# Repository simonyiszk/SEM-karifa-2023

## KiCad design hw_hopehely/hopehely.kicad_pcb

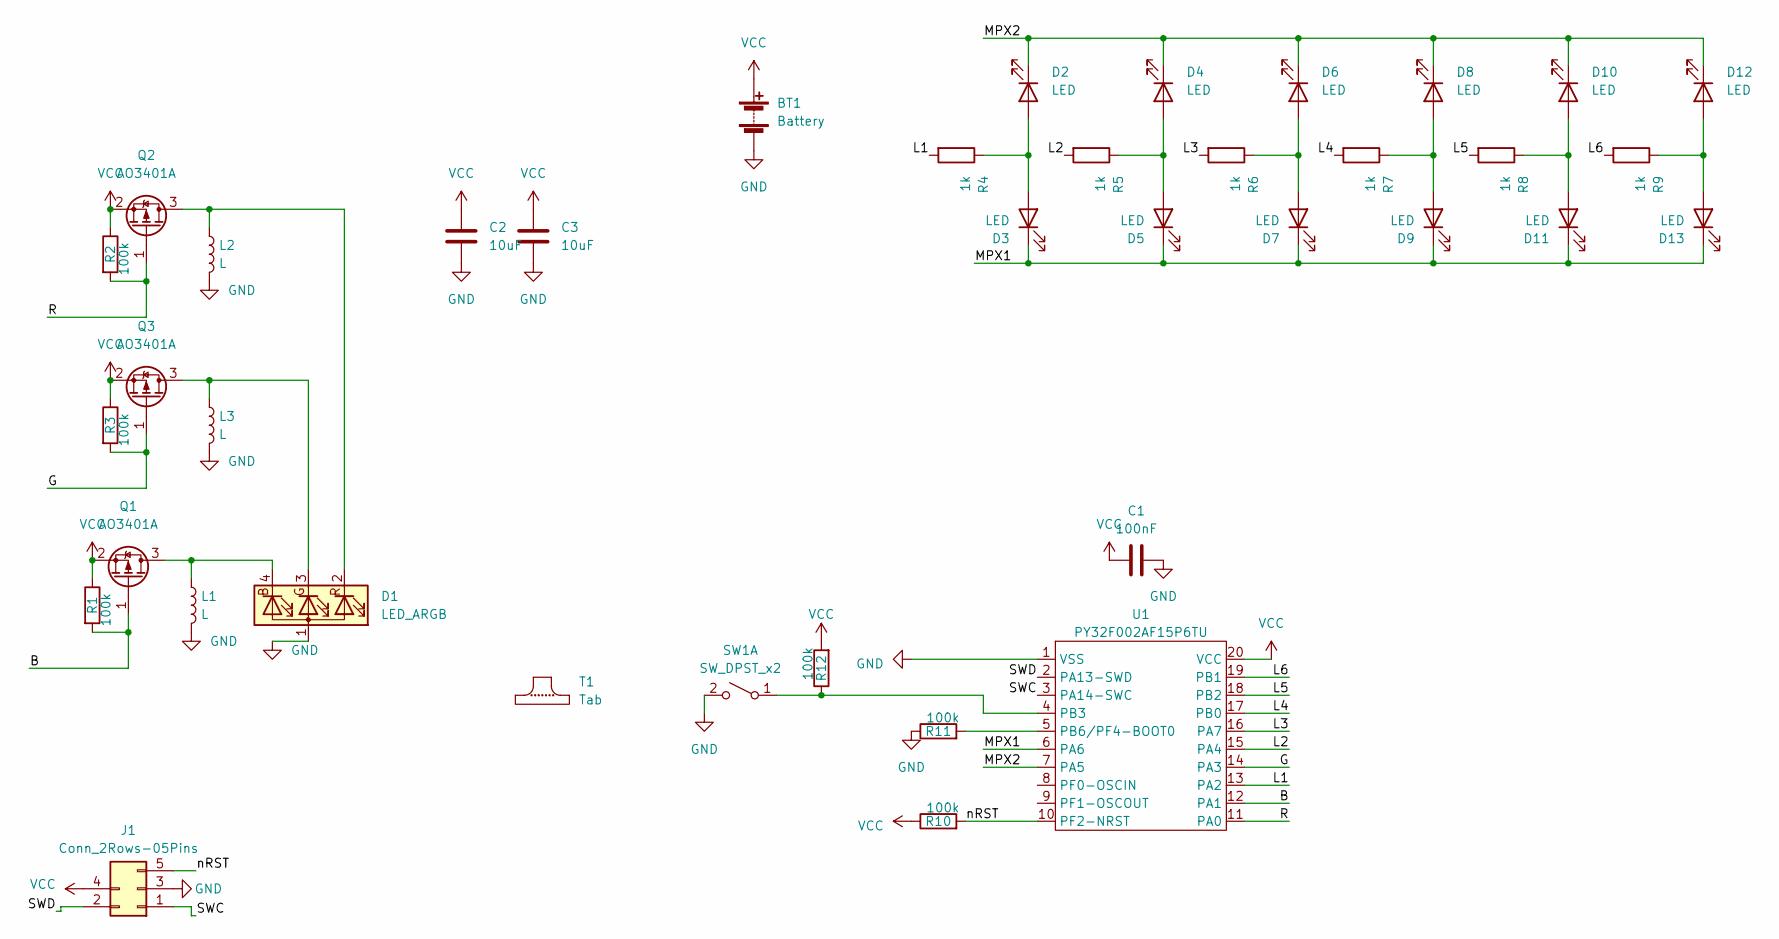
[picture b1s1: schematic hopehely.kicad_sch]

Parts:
BT1: Battery; CR2032_Holder
C1: 100nF; C_0805_2012Metric
C2, C3: 10uF; C_0805_2012Metric
D1: LED_ARGB; LED_RGB_Wuerth-PLCC4_3.2x2.8mm_150141M173100
D2, D3, D4, D5, D6, D7, D8, D9, D10, D11, D12, D13: LED; LED_0805_2012Metric
J1: Conn_2Rows-05Pins; ProgConnector_5pin
L1, L2, L3: L; L_1008_2520Metric
Q1, Q2, Q3: AO3401A; SOT-23
R1, R2, R3, R10, R11, R12: 100k; R_0603_1608Metric
R4, R5, R6, R7, R8, R9: 1k; R_0603_1608Metric
SW1: SW_DPST_x2; SW_SPST_TL3342
T1: Tab
U1: PY32F002AF15P6TU; TSSOP-20_4.4x6.5mm_P0.65mm

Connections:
/B: Q1.1 (G), R1.2, U1.12 (PA1)
/G: Q3.1 (G), R3.2, U1.14 (PA3)
/L1: R4.2, U1.13 (PA2)
/L2: R5.2, U1.15 (PA4)
/L3: R6.2, U1.16 (PA7)
/L4: R7.2, U1.17 (PB0)
/L5: R8.2, U1.18 (PB2)
/L6: R9.2, U1.19 (PB1)
/MPX1: D3.1 (K), D5.1 (K), D7.1 (K), D9.1 (K), D11.1 (K), D13.1 (K), U1.6 (PA6)
/MPX2: D2.1 (K), D4.1 (K), D6.1 (K), D8.1 (K), D10.1 (K), D12.1 (K), U1.7 (PA5)
/R: Q2.1 (G), R2.2, U1.11 (PA0)
/SWC: J1.1, U1.3 (PA14-SWC)
/SWD: J1.2, U1.2 (PA13-SWD)
/nRST: J1.5, R10.2, U1.10 (PF2-NRST)
GND: BT1.2 (-), C1.1, C2.2, C3.2, D1.1 (A), J1.3, L1.2, L2.2, L3.2, R11.1, SW1.2 (B), U1.1 (VSS)
unnamed: D1.4 (BK), L1.1, Q1.3 (D)
unnamed: D1.3 (GK), L3.1, Q3.3 (D)
unnamed: D1.2 (RK), L2.1, Q2.3 (D)
unnamed: D2.2 (A), D3.2 (A), R4.1
unnamed: D4.2 (A), D5.2 (A), R5.1
unnamed: D6.2 (A), D7.2 (A), R6.1
unnamed: D8.2 (A), D9.2 (A), R7.1
unnamed: D10.2 (A), D11.2 (A), R8.1
unnamed: D12.2 (A), D13.2 (A), R9.1
unnamed: R12.1, SW1.1 (A), U1.4 (PB3)
unnamed: R11.2, U1.5 (PB6/PF4-BOOT0)
VCC: BT1.1 (+), C1.2, C2.1, C3.1, J1.4, Q1.2 (S), Q2.2 (S), Q3.2 (S), R1.1, R2.1, R3.1, R10.1, R12.2, U1.20 (VCC)

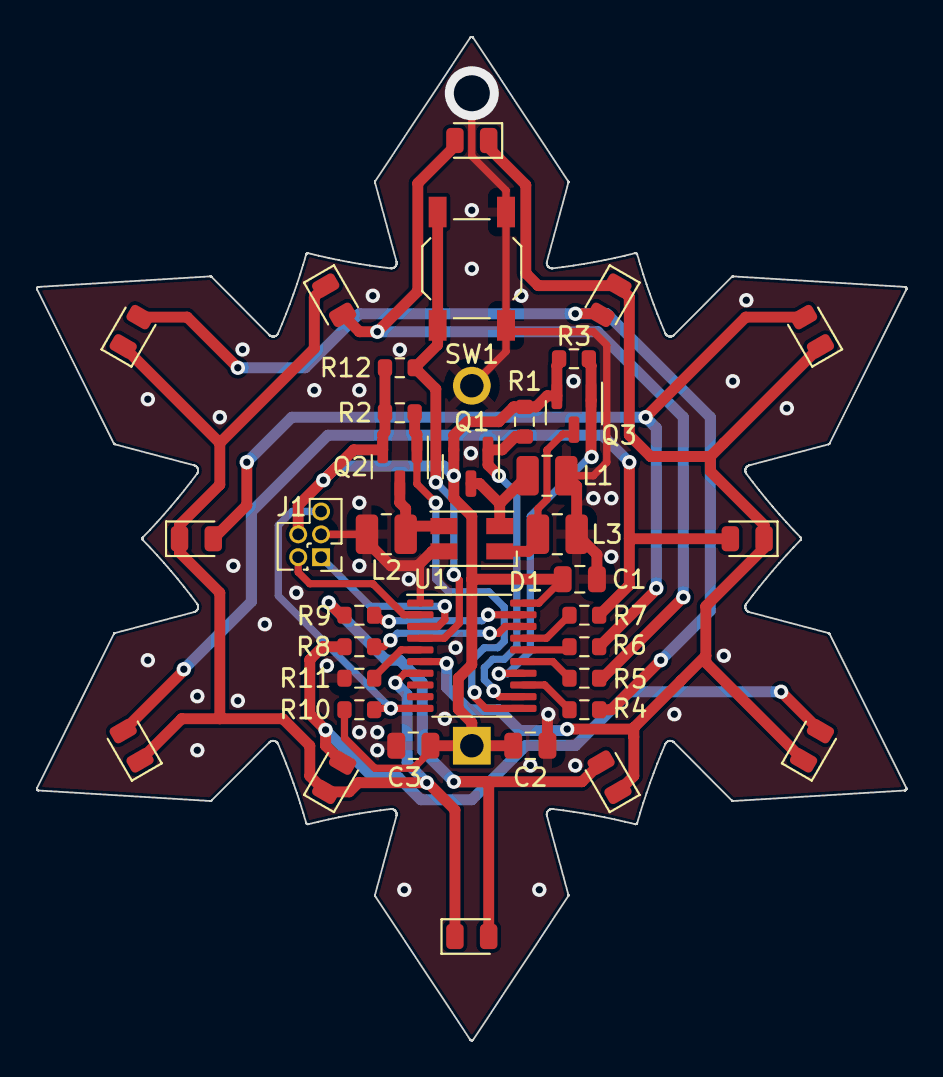
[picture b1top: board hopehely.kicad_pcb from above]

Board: 2 copper layers, 48.3 x 55.8 mm, 44 parts (1 on the bottom side), 27 nets.

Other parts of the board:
T1#2, T1#3, T1#4, T1#5, T1#6: Tab

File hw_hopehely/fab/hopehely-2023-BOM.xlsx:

Comment | Designator | Footprint | JLCPCB Part #（optional）
PY32F002AF15P6TU | U1 | TSSOP-20 | C5292059
1mH | L1, L2, L3 | 1008 | C223217
AO3401A | Q1, Q2, Q3 | SOT-23 | C15127
100k | R1, R2, R3, R10, R11, R12 | 0603 | C25803
RGB LED | D1 | 3528(mm) | C2827321
Yellow LED | D2, D3, D4, D5, D6, D7, D8, D9, D10, D11, D12, D13 | 0805 | C2296
1k | R4, R5, R6, R7, R8, R9 | 0603 | C21190
SW_DPST_x2 | SW1 | SMD | C318884
10uF | C2, C3 | 0805 | C15850
100nF | C1 | 0805 | C49678
